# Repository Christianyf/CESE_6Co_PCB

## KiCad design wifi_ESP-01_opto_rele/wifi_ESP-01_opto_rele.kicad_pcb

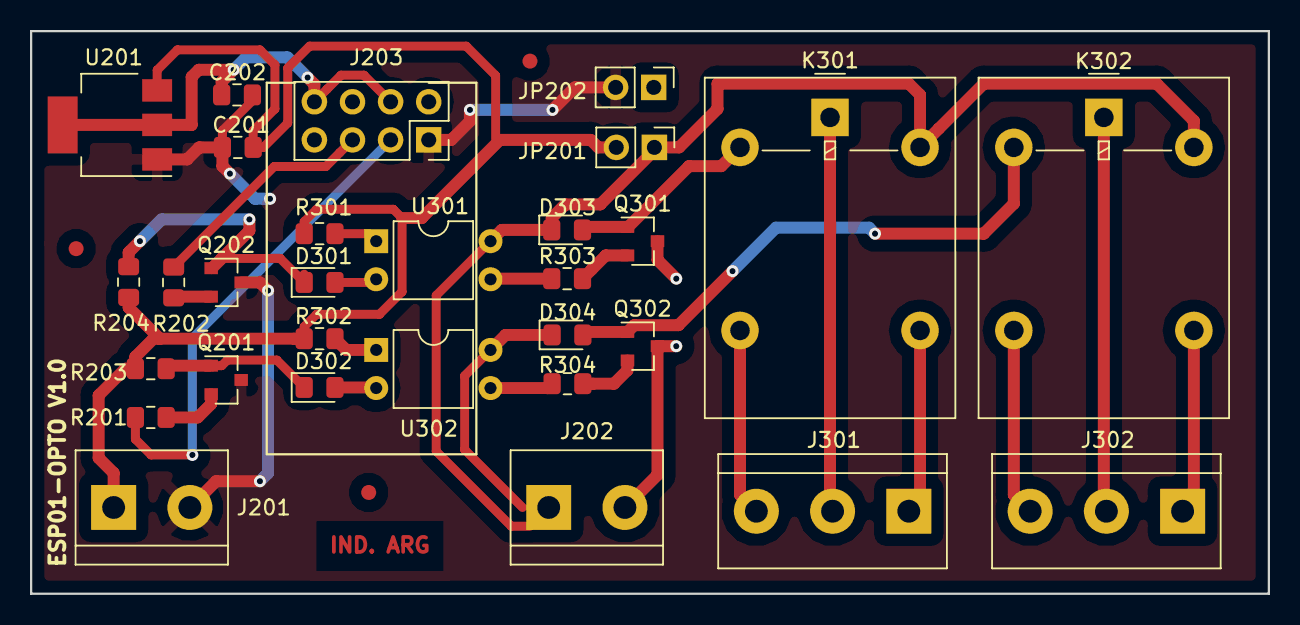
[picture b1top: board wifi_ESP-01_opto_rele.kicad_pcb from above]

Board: 2 copper layers, 82.5 x 37.5 mm, 33 parts (0 on the bottom side), 27 nets.

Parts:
C201: 100nF; C_0805_2012Metric_Pad1.15x1.40mm_HandSolder
C202: 10uF; C_0805_2012Metric_Pad1.15x1.40mm_HandSolder
D301, D302: LED; LED_0805_2012Metric_Pad1.15x1.40mm_HandSolder
D303, D304: 1N4148; D_0805_2012Metric_Pad1.15x1.40mm_HandSolder
F101, F102, F103: MountingHole; Fiducial_1mm_Dia_2mm_Outer
J201, J202: Conn_01x02; TerminalBlock_bornier-2_P5.08mm
J203: Conn_02x04_Odd_Even_MountingPin; PinSocket_2x04_P2.54mm_Vertical
J301, J302: Conn_01x03; TerminalBlock_bornier-3_P5.08mm
JP201, JP202: Jumper; PinHeader_1x02_P2.54mm_Vertical
K301, K302: G5LE-1; Relay_SPDT_Omron-G5LE-1
Q201, Q202, Q301, Q302: BC547; SOT-23
R201, R202: 47k; R_0805_2012Metric_Pad1.15x1.40mm_HandSolder
R203, R204, R303, R304: 1k; R_0805_2012Metric_Pad1.15x1.40mm_HandSolder
R301, R302: 200; R_0805_2012Metric_Pad1.15x1.40mm_HandSolder
U201: LD1117S33TR_SOT223; SOT-223-3_TabPin2
U301, U302: PC817; DIP-4_W7.62mm

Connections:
+5V: D303.1, D304.1, J202.1, JP201.1, K301.5, K302.5, U301.4, U302.4
+5VA: C201.1, J201.1, JP201.2, R203.1, R204.1, R301.1, R302.1, U201.3
/ESP01/GPIO0: D301.1, Q202.1, R204.2
/ESP01/GPIO1: D302.1, Q201.1, R203.2
/Opto-aclope/COM0: J301.2, K301.1
/Opto-aclope/COM1: J302.2, K302.1
GND: J202.2, JP202.1, Q301.3, Q302.3
GNDA: C201.2, C202.2, J201.2, J203.1, JP202.2, Q201.3, Q202.3, U201.1
unnamed: C202.1, J203.6, J203.8, U201.2
unnamed: D301.2, U301.2
unnamed: D302.2, U302.2
unnamed: D303.2, K301.2, Q301.1
unnamed: D304.2, K302.2, Q302.1
unnamed: J203.2, R201.1
unnamed: J203.3, R202.1
unnamed: J301.1, K301.4
unnamed: J301.3, K301.3
unnamed: J302.1, K302.4
unnamed: J302.3, K302.3
unnamed: Q201.2, R201.2
unnamed: Q202.2, R202.2
unnamed: Q301.2, R303.1
unnamed: Q302.2, R304.1
unnamed: R301.2, U301.1
unnamed: R302.2, U302.1
unnamed: R303.2, U301.3
unnamed: R304.2, U302.3

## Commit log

2018-10-07 Primer avance
2018-10-09 Segunda revisión
2018-10-09 actualización
2018-10-20 Correcciones_revisor
2018-10-20 Correcciones_revisor_2
2018-10-23 correcciones pcb
2018-11-21 correcciones v2
2018-11-22 revisión final
